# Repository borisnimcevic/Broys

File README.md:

# Watchular (ESP32-C3 based modular watch)

### Name origin:
* watch + modular

### Bill Of Materials
|Component  |Quantity |Link   |
|-----      |-----    |-----  |
|ESP32-C3   |1        |[digikey](https://www.digikey.se/en/products/detail/espressif-systems/ESP32-C3-MINI-1-N4-A/15817506) |
|or with embedded flash (ESP32-C3FN4)   |1        |[digikey](https://www.digikey.se/en/products/detail/espressif-systems/ESP32-C3FH4/14115592) |
|Battery charger|1        |[digikey](https://www.digikey.se/en/products/detail/microchip-technology/MCP73832T-2DCI-OT/1223150) |
|Battery connector|1        |[digikey](https://www.digikey.se/en/products/detail/w%C3%BCrth-elektronik/665102131822/5047757?s=N4IgTCBcDaIGxwKwEYAMZkGZkA4wQF0BfIA) |
|Button|2        |[digikey](https://www.digikey.se/en/products/detail/e-switch/TL3301AF260QG/378995?s=N4IgTCBcDaICoBkDMSAMBGAggMTANlQEUBxEAXQF8g) |
|Ceramic antenna (chip antenna)|1        |[digikey](https://www.digikey.se/en/products/detail/johanson-technology-inc/2450AT18A100E/1560676) |
|Ceramic capacitor 100nF 0402 |4        |[digikey](https://www.digikey.se/en/products/detail/taiyo-yuden/EMK105B7104KV-F/1004039) |
|Ceramic capacitor 1pF 0402 |1        |[digikey](https://www.digikey.se/en/products/detail/walsin-technology-corporation/0402N1R0B500CT/9354767) |
|Ceramic capacitor 1uF 0603 |2        |[digikey](https://www.digikey.se/en/products/detail/taiyo-yuden/EMK107BJ105KA-T/930603) |
|Ceramic capacitor 2.2uF 0603 |2        |[digikey](https://www.digikey.se/en/products/detail/taiyo-yuden/EMK107BJ225KA-T/1004018) |
|Ceramic capacitor 4.7uF 0402 |1        |[digikey](https://www.digikey.se/en/products/detail/murata-electronics/GRT155R60J475ME13J/13904800) |
|Ceramic capacitor 4.7uF 0603 |2        |[digikey](https://www.digikey.se/en/products/detail/taiyo-yuden/JMK107BJ475KA-T/1169922) |
|Ceramic capacitor 8pF 0402 |2        |[digikey](https://www.digikey.se/en/products/detail/taiyo-yuden/UMK105CH080DVHF/6563655) |
|Ceramic inductor 2.7nH |1        |[digikey](https://www.digikey.se/en/products/detail/johanson-technology-inc/L-07C2N7SV6T/1830166?s=N4IgTCBcDaIDIFoAMB2AwmAcigygNQDYAVEAXQF8g) |
|Ceramic inductor 3.9nH |1        |[digikey](https://www.digikey.se/en/products/detail/johanson-technology-inc/L-07C3N9SV6T/1915227) |
|Crystal 16MHz|1        |[digikey](https://www.digikey.se/en/products/detail/txc-corporation/8Y-16-000MAHQ-T/6130681) |
|FLASH 4MBIT   |1        |[digikey](https://www.digikey.se/en/products/detail/winbond-electronics/W25Q16JVSSIM/12143335) |
|LDO 3.3V 600mA|1        |[digikey](https://www.digikey.se/en/products/detail/diodes-incorporated/AP7366-33W5-7/9867322) |
|LED Orange 0402|1        |[digikey](https://www.digikey.se/en/products/detail/sunled/XZMOK68W-2/4902071) |
|LED Red 0603|30        |[digikey](https://www.digikey.se/en/products/detail/liteon/LTST-C191KRKT/386837) |
|Male Header 16 positions (1 row)|2        |[digikey](https://www.digikey.se/en/products/detail/adam-tech/PH1-16-UA/9830344) |
|N-channel MOSFET|4        |[digikey](https://www.digikey.se/en/products/detail/toshiba-semiconductor-and-storage/T2N7002AK-LM/5298028) |
|P-channel MOSFET|1        |[digikey](https://www.digikey.se/en/products/detail/diodes-incorporated/DMP2004K-7/1774201) |
|Resistor 0 ohm 0402   |1        |[digikey](https://www.digikey.se/en/products/detail/yageo/RC0402JR-070RP/4935294) |
|Resistor 100k 0402   |1        |[digikey](https://www.digikey.se/en/products/detail/yageo/RC0402JR-07100KL/726416) |
|Resistor 10k 0402   |4        |[digikey](https://www.digikey.se/en/products/detail/yageo/RC0402JR-0710KL/726418) |
|Resistor 1k 0402   |5        |[digikey](https://www.digikey.se/en/products/detail/delta-electronics-cyntec/PFR05S-102-JNH/9761533) |
|Resistor 2k 0402   |1        |[digikey](https://www.digikey.se/en/products/detail/yageo/RC0402JR-072KL/726434) |
|Resistor 5.1k 1% 0402   |2        |[digikey](https://www.digikey.se/en/products/detail/yageo/RC0402FR-135K1L/14286364) |
|Resistor 560 0402   |9        |[digikey](https://www.digikey.se/en/products/detail/yageo/RC0402JR-07560RL/726492) |
|Schottky|1        |[digikey](https://www.digikey.se/en/products/detail/smc-diode-solutions/DSS16U/8341861) |
|USB-C|1        |[digikey](https://www.digikey.se/en/products/detail/gct/USB4105-GF-A/11198441) |
|ESD-protector|1        |[digikey](https://www.digikey.se/en/products/detail/smc-diode-solutions/SR05/10820120) |

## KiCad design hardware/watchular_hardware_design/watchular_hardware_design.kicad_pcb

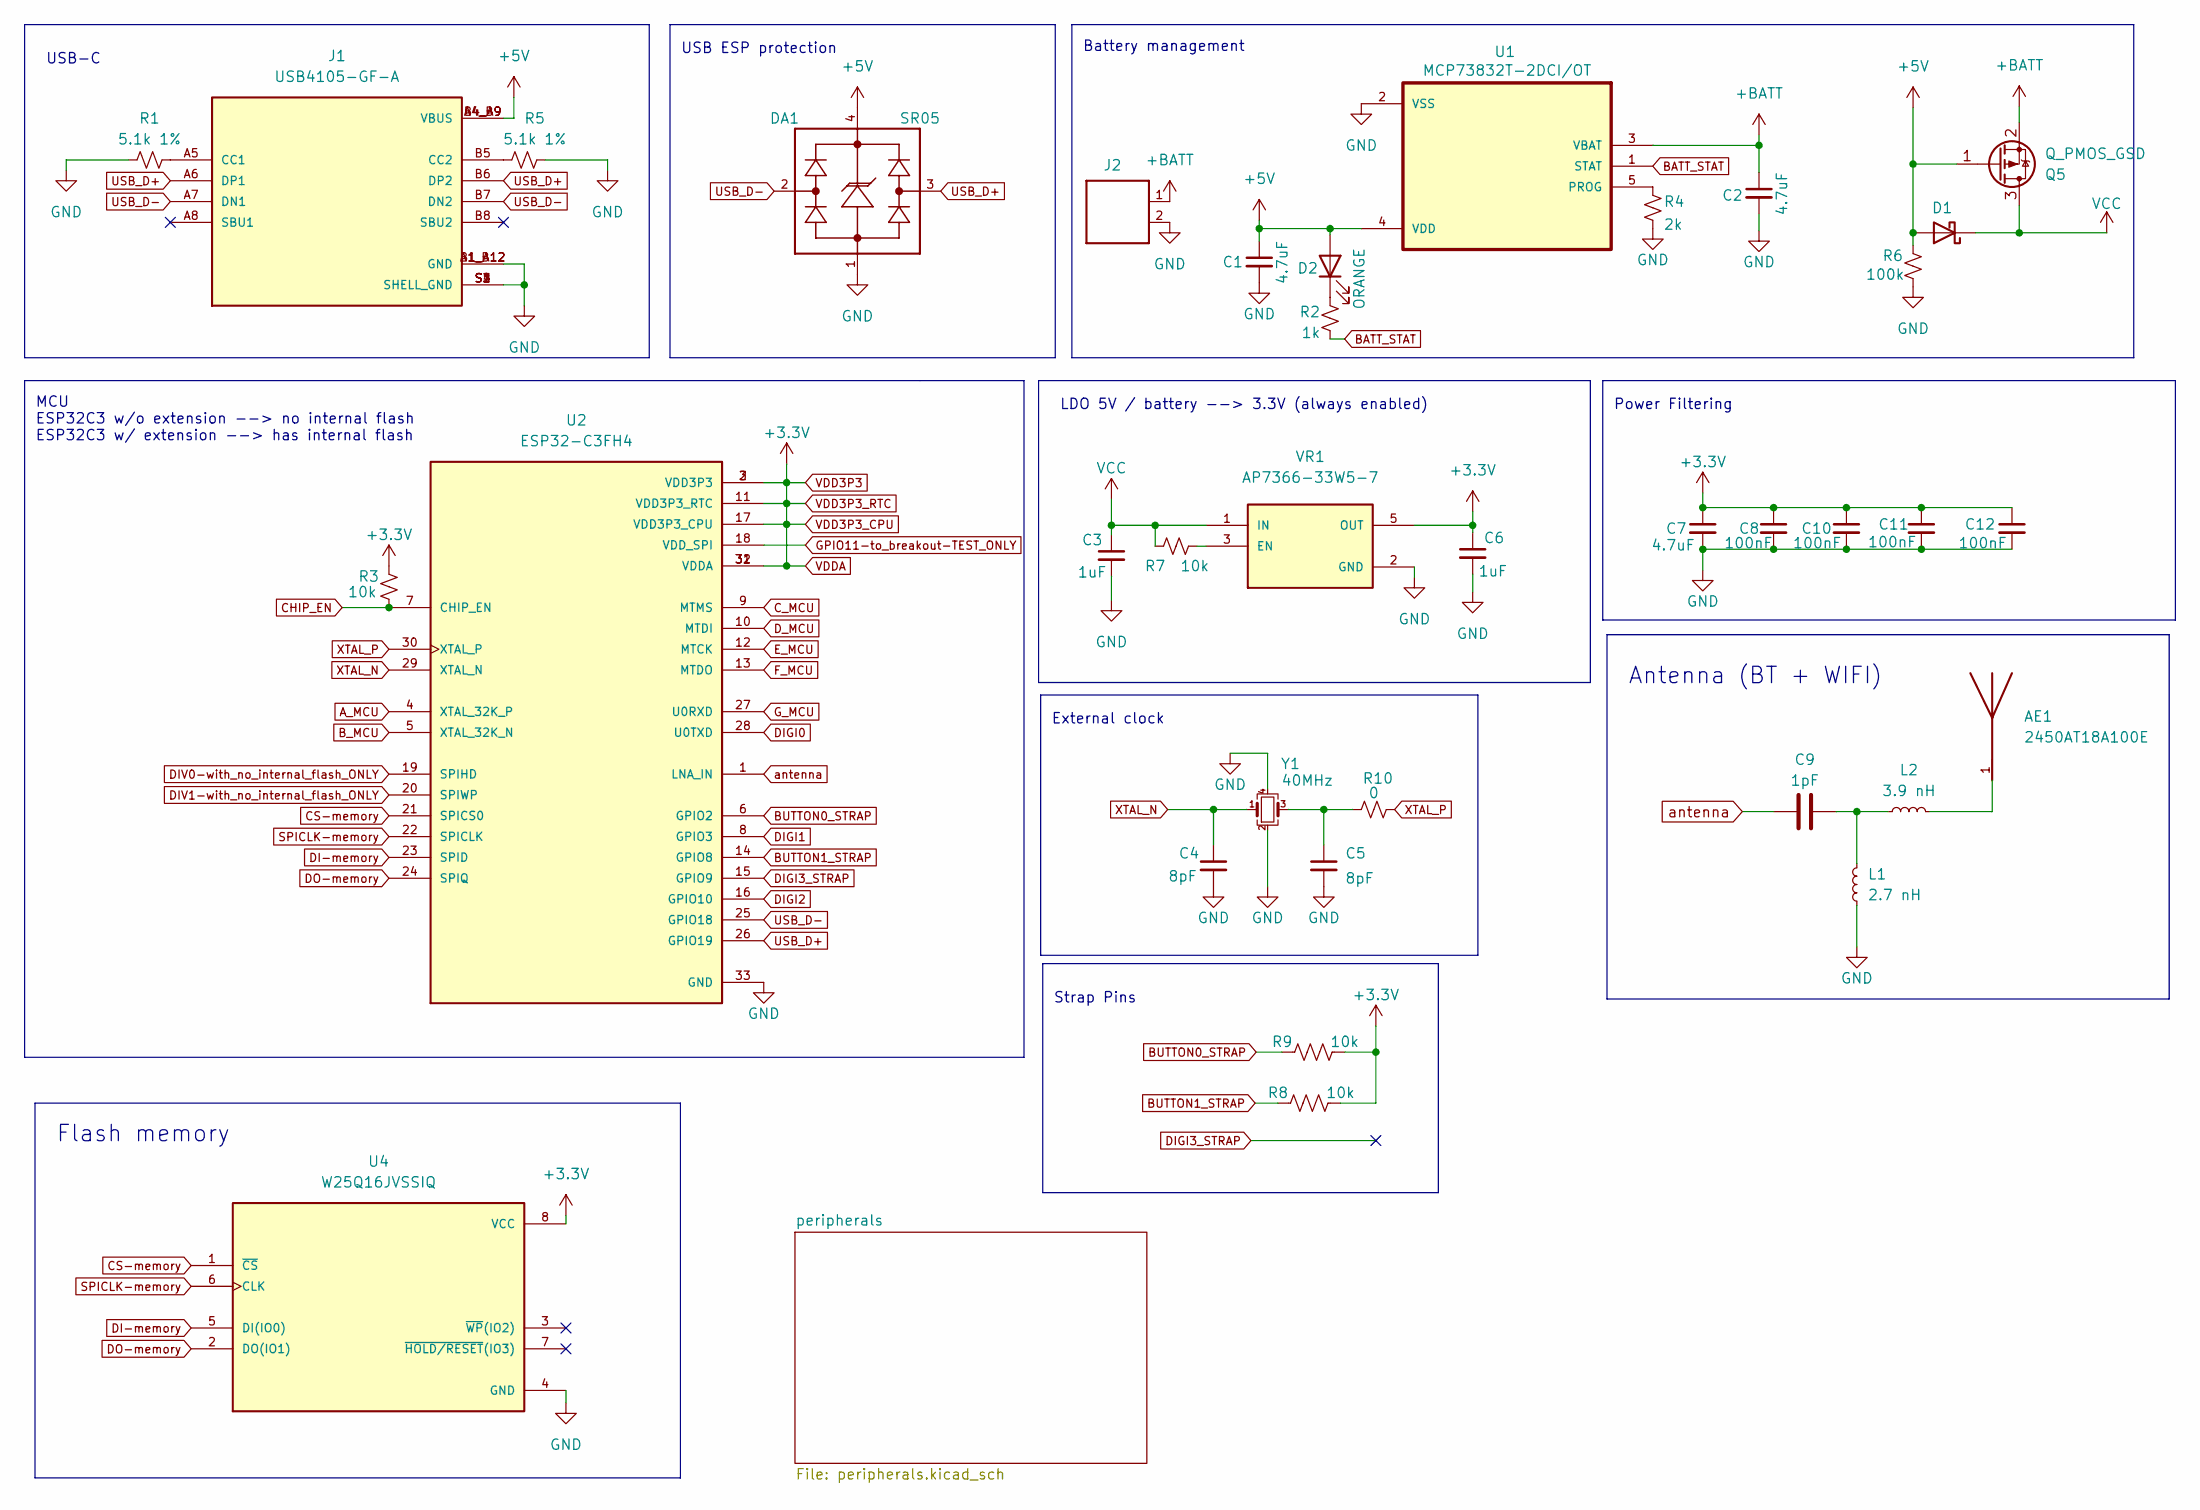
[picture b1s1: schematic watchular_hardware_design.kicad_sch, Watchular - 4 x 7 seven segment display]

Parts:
AE1: 2450AT18A100E; ANTC3216X140N; PARTREV 1.3
C1, C2: 4.7uF; C_0603_1608Metric_Pad1.08x0.95mm_HandSolder
C3, C6: 1uF; C_0603_1608Metric_Pad1.08x0.95mm_HandSolder
C4, C5: 8pF; C_0402_1005Metric_Pad0.74x0.62mm_HandSolder
C7: 4.7uF; L_0402_1005Metric
C8, C10, C11, C12: 100nF; L_0402_1005Metric
C9: 1pF; C_0402_1005Metric
D1: D_Schottky; D_SOD-123F
D2: ORANGE; LED_0402_1005Metric_Pad0.77x0.64mm_HandSolder
DA1: SR05; SOT143
J1: USB4105-GF-A; GCT_USB4105-GF-A; PARTREV A3
J2: 665102131822
L1: 2.7 nH; L_0402_1005Metric
L2: 3.9 nH; L_0402_1005Metric
Q5: Q_PMOS_GSD; SOT91P240X105-3N
R1, R5: 5.1k 1%; R_0402_1005Metric_Pad0.72x0.64mm_HandSolder
R2: 1k; R_0402_1005Metric_Pad0.72x0.64mm_HandSolder
R3, R7, R8, R9: 10k; R_0402_1005Metric_Pad0.72x0.64mm_HandSolder
R4: 2k; R_0402_1005Metric_Pad0.72x0.64mm_HandSolder
R6: 100k; R_0402_1005Metric_Pad0.72x0.64mm_HandSolder
R10: 0; R_0402_1005Metric_Pad0.72x0.64mm_HandSolder
U1: MCP73832T-2DCI/OT; SOT95P280X145-5N
U2: ESP32-C3FH4; QFN50P500X500X90-33N; PARTREV V1.0
U4: W25Q16JVSSIQ; SOIC127P790X216-8N
VR1: AP7366-33W5-7; SOT95P285X140-5N; PARTREV 1-2
Y1: 40MHz; Crystal_SMD_2016-4Pin_2.0x1.6mm

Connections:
+5V: C1.1, D1.2 (A), D2.2 (A), DA1.4, J1.A4_B9 (VBUS), J1.B4_A9 (VBUS), Q5.1 (G), R6.1, U1.4 (VDD); also elsewhere on the board
+BATT: C2.1, J2.1, Q5.2 (S), U1.3 (VBAT); also elsewhere on the board
A_MCU: U2.4 (XTAL_32K_P); also elsewhere on the board
BATT_STAT: R2.2, U1.1 (STAT)
BUTTON0_STRAP: R9.1, U2.6 (GPIO2); also elsewhere on the board
BUTTON1_STRAP: R8.1, U2.14 (GPIO8); also elsewhere on the board
B_MCU: U2.5 (XTAL_32K_N); also elsewhere on the board
CHIP_EN: R3.2, U2.7 (CHIP_EN); also elsewhere on the board
CS-memory: U2.21 (SPICS0), U4.1 (~CS); also elsewhere on the board
C_MCU: U2.9 (MTMS); also elsewhere on the board
DI-memory: U2.23 (SPID), U4.5 (DI(IO0)); also elsewhere on the board
DIGI0: U2.28 (U0TXD); also elsewhere on the board
DIGI1: U2.8 (GPIO3); also elsewhere on the board
DIGI2: U2.16 (GPIO10); also elsewhere on the board
DIGI3_STRAP: U2.15 (GPIO9); also elsewhere on the board
DIV0-with_no_internal_flash_ONLY: U2.19 (SPIHD); also elsewhere on the board
DIV1-with_no_internal_flash_ONLY: U2.20 (SPIWP); also elsewhere on the board
DO-memory: U2.24 (SPIQ), U4.2 (DO(IO1)); also elsewhere on the board
D_MCU: U2.10 (MTDI); also elsewhere on the board
E_MCU: U2.12 (MTCK); also elsewhere on the board
F_MCU: U2.13 (MTDO); also elsewhere on the board
GND: C1.2, C2.2, C3.2, C4.2, C5.2, C6.2, C7.2, C8.2, C10.2, C11.2, C12.2, DA1.1, J1.A1_B12 (GND), J1.B1_A12 (GND), J1.S1 (SHELL_GND), J1.S2 (SHELL_GND), J1.S3 (SHELL_GND), J1.S4 (SHELL_GND), J2.2, L1.1, R1.1, R4.2, R5.2, R6.2, U1.2 (VSS), U2.33 (GND), U4.4 (GND), VR1.2 (GND), Y1.2, Y1.4; also elsewhere on the board
GPIO11-to_breakout-TEST_ONLY: U2.18 (VDD_SPI); also elsewhere on the board
G_MCU: U2.27 (U0RXD); also elsewhere on the board
unnamed: AE1.1, L2.2
unnamed: C5.1, R10.1, Y1.3
unnamed: C9.2, L1.2, L2.1
unnamed: D2.1 (K), R2.1
unnamed: J1.A5 (CC1), R1.2
unnamed: J1.B5 (CC2), R5.1
unnamed: R4.1, U1.5 (PROG)
unnamed: R7.2, VR1.3 (EN)
SPICLK-memory: U2.22 (SPICLK), U4.6 (CLK); also elsewhere on the board
USB_D+: DA1.3, J1.A6 (DP1), J1.B6 (DP2), U2.26 (GPIO19); also elsewhere on the board
USB_D-: DA1.2, J1.A7 (DN1), J1.B7 (DN2), U2.25 (GPIO18); also elsewhere on the board
VCC: C3.1, D1.1 (K), Q5.3 (D), R7.1, VR1.1 (IN)
VDD3P3: C6.1, C7.1, C8.1, C10.1, C11.1, C12.1, R3.1, R8.2, R9.2, U2.2 (VDD3P3), U2.3 (VDD3P3), U2.11 (VDD3P3_RTC), U2.17 (VDD3P3_CPU), U2.31 (VDDA), U2.32 (VDDA), U4.8 (VCC), VR1.5 (OUT); also elsewhere on the board
XTAL_N: C4.1, U2.29 (XTAL_N), Y1.1; also elsewhere on the board
XTAL_P: R10.2, U2.30 (XTAL_P); also elsewhere on the board
antenna: C9.1, U2.1 (LNA_IN)

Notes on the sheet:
USB-C
LDO 5V / battery --> 3.3V (always enabled)
Battery management
Flash memory
Power Filtering
Antenna (BT + WIFI)
External clock
MCU ESP32C3 w/o extension --> no internal flash ESP32C3 w/ extension --> has internal flash
Strap Pins
USB ESP protection

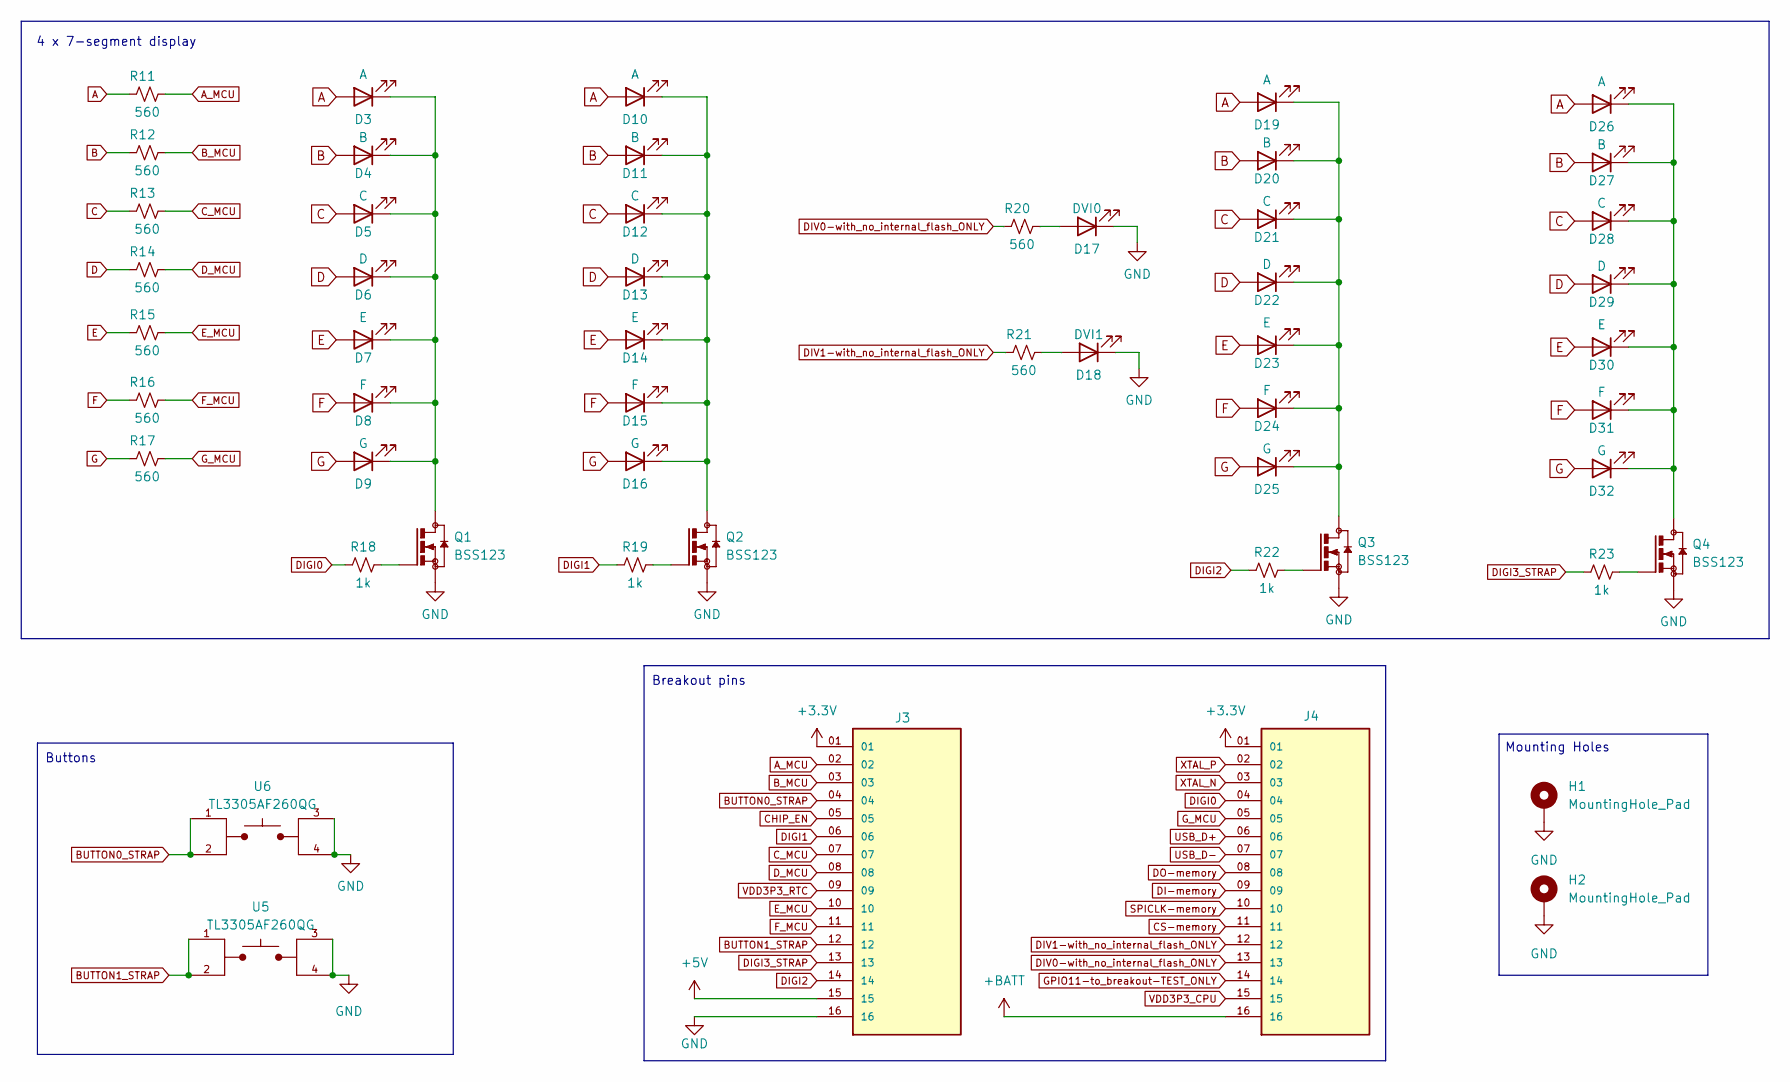
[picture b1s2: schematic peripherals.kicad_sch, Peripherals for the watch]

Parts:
D3, D10, D19, D26: A; LED_0603_custom_boris
D4, D11, D20, D27: B; LED_0603_custom_boris
D5, D12, D21, D28: C; LED_0603_custom_boris
D6, D13, D22, D29: D; LED_0603_custom_boris
D7, D14, D23, D30: E; LED_0603_custom_boris
D8, D15, D24, D31: F; LED_0603_custom_boris
D9, D16, D25, D32: G; LED_0603_custom_boris
D17: DVI0; LED_0603_custom_boris
D18: DVI1; LED_0603_custom_boris
H1, H2: MountingHole_Pad; MountingHole_2.2mm_M2_Pad_Via
J3, J4: TSW-116-07-H-S; SAMTEC_TSW-116-07-H-S; PARTREV R
Q1, Q2, Q3, Q4: BSS123; SOT23
R11, R12, R13, R14, R15, R16, R17, R20, R21: 560; R_0402_1005Metric_Pad0.72x0.64mm_HandSolder
R18, R19, R22, R23: 1k; R_0402_1005Metric_Pad0.72x0.64mm_HandSolder
U5, U6: TL3305AF260QG; SW_TL3305AF260QG; PARTREV C

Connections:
+5V: J3.15; also elsewhere on the board
+BATT: J4.16; also elsewhere on the board
A: D3.2 (A), D10.2 (A), D19.2 (A), D26.2 (A), R11.1
A_MCU: J3.02, R11.2; also elsewhere on the board
B: D4.2 (A), D11.2 (A), D20.2 (A), D27.2 (A), R12.1
BUTTON0_STRAP: J3.04, U6.1, U6.2; also elsewhere on the board
BUTTON1_STRAP: J3.12, U5.1, U5.2; also elsewhere on the board
B_MCU: J3.03, R12.2; also elsewhere on the board
C: D5.2 (A), D12.2 (A), D21.2 (A), D28.2 (A), R13.1
CHIP_EN: J3.05; also elsewhere on the board
CS-memory: J4.11; also elsewhere on the board
C_MCU: J3.07, R13.2; also elsewhere on the board
D: D6.2 (A), D13.2 (A), D22.2 (A), D29.2 (A), R14.1
DI-memory: J4.09; also elsewhere on the board
DIGI0: J4.04, R18.1; also elsewhere on the board
DIGI1: J3.06, R19.1; also elsewhere on the board
DIGI2: J3.14, R22.1; also elsewhere on the board
DIGI3_STRAP: J3.13, R23.1; also elsewhere on the board
DIV0-with_no_internal_flash_ONLY: J4.13, R20.1; also elsewhere on the board
DIV1-with_no_internal_flash_ONLY: J4.12, R21.1; also elsewhere on the board
DO-memory: J4.08; also elsewhere on the board
D_MCU: J3.08, R14.2; also elsewhere on the board
E: D7.2 (A), D14.2 (A), D23.2 (A), D30.2 (A), R15.1
E_MCU: J3.10, R15.2; also elsewhere on the board
F: D8.2 (A), D15.2 (A), D24.2 (A), D31.2 (A), R16.1
F_MCU: J3.11, R16.2; also elsewhere on the board
G: D9.2 (A), D16.2 (A), D25.2 (A), D32.2 (A), R17.1
GND: D17.1 (K), D18.1 (K), H1.1, H2.1, J3.16, Q1.2, Q2.2, Q3.2, Q4.2, U5.3, U5.4, U6.3, U6.4; also elsewhere on the board
GPIO11-to_breakout-TEST_ONLY: J4.14; also elsewhere on the board
G_MCU: J4.05, R17.2; also elsewhere on the board
unnamed: D3.1 (K), D4.1 (K), D5.1 (K), D6.1 (K), D7.1 (K), D8.1 (K), D9.1 (K), Q1.3
unnamed: D10.1 (K), D11.1 (K), D12.1 (K), D13.1 (K), D14.1 (K), D15.1 (K), D16.1 (K), Q2.3
unnamed: D17.2 (A), R20.2
unnamed: D18.2 (A), R21.2
unnamed: D19.1 (K), D20.1 (K), D21.1 (K), D22.1 (K), D23.1 (K), D24.1 (K), D25.1 (K), Q3.3
unnamed: D26.1 (K), D27.1 (K), D28.1 (K), D29.1 (K), D30.1 (K), D31.1 (K), D32.1 (K), Q4.3
unnamed: Q1.1, R18.2
unnamed: Q2.1, R19.2
unnamed: Q3.1, R22.2
unnamed: Q4.1, R23.2
SPICLK-memory: J4.10; also elsewhere on the board
USB_D+: J4.06; also elsewhere on the board
USB_D-: J4.07; also elsewhere on the board
VDD3P3: J3.01, J3.09, J4.01, J4.15; also elsewhere on the board
XTAL_N: J4.03; also elsewhere on the board
XTAL_P: J4.02; also elsewhere on the board

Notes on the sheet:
Breakout pins
4 x 7-segment display
Buttons
Mounting Holes

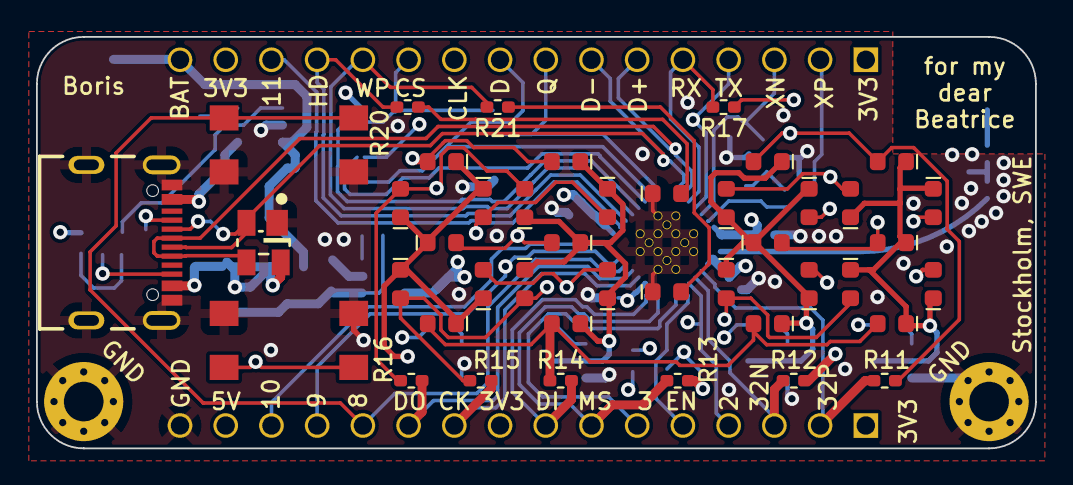
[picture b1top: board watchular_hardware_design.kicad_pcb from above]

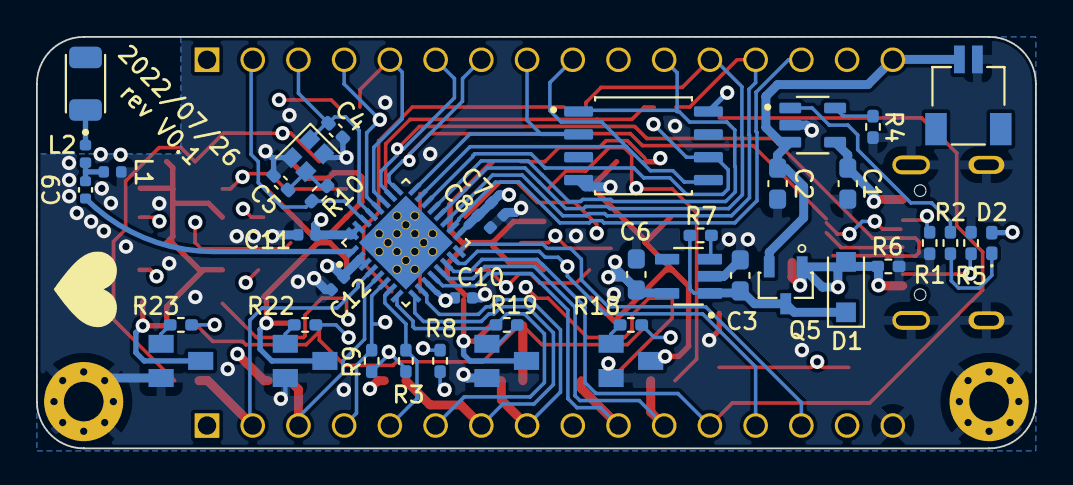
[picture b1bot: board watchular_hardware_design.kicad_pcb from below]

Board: 4 copper layers, 55.5 x 22.9 mm, 89 parts (42 on the bottom side), 57 nets.

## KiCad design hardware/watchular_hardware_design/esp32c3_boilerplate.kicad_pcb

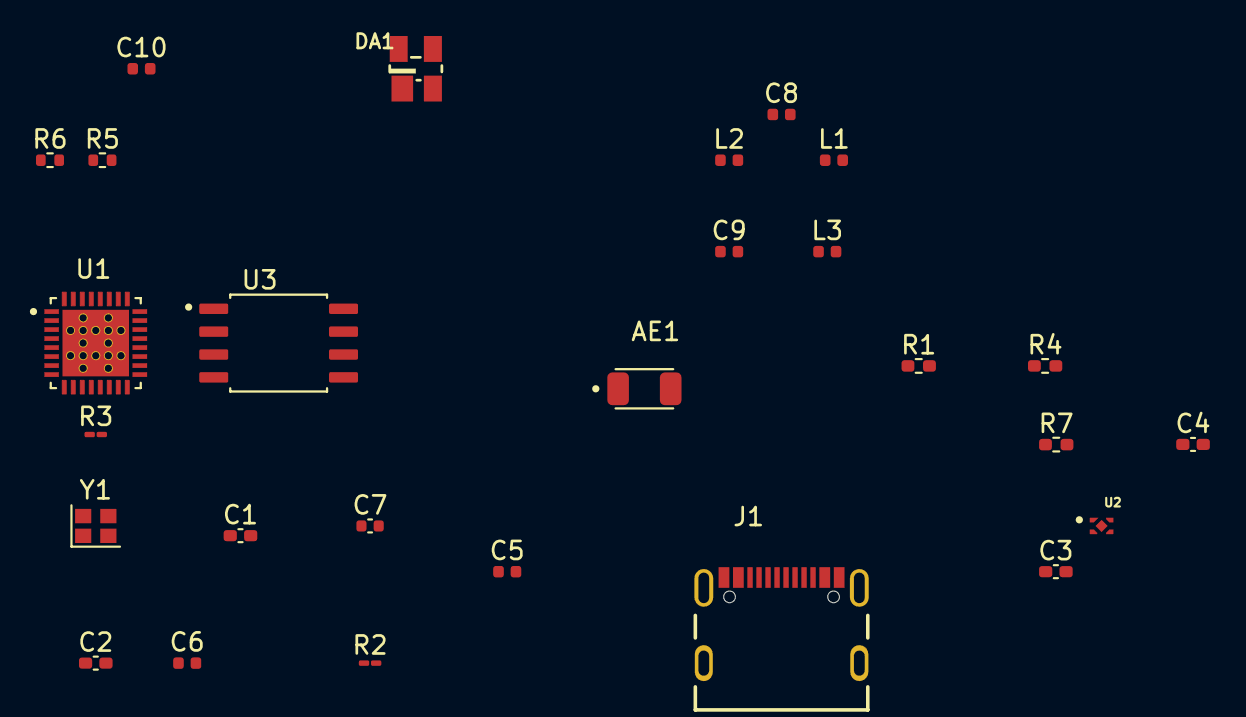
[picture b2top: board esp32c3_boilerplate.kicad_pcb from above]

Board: 2 copper layers, 27 parts (0 on the bottom side), 22 nets, no tracks yet.

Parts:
AE1: 2450AT18A100E; ANTC3216X140N
C1, C2: 8pF; C_0402_1005Metric_Pad0.74x0.62mm_HandSolder
C3, C4: 2.2uF; C_0402_1005Metric_Pad0.74x0.62mm_HandSolder
C5: 4.7uF; L_0402_1005Metric
C6, C8: 100nF; L_0402_1005Metric
C7: 1pF; C_0402_1005Metric
C9: 1uF; L_0402_1005Metric
C10: 10nF; L_0402_1005Metric
DA1: SR05; SOT143
J1: USB4105-GF-A; GCT_USB4105-GF-A
L1: 2.7 nH; L_0402_1005Metric
L2: 3.9 nH; L_0402_1005Metric
L3: 39nH; L_0402_1005Metric
R1, R4: 5.1k 1%; R_0402_1005Metric_Pad0.72x0.64mm_HandSolder
R2: 0; R_01005_0402Metric_Pad0.57x0.30mm_HandSolder
R3: 10k; R_01005_0402Metric_Pad0.57x0.30mm_HandSolder
R5, R6: 10k; R_0402_1005Metric
R7: 10k; R_0402_1005Metric_Pad0.72x0.64mm_HandSolder
U1: ESP32-C3FH4; QFN50P500X500X90-33N
U2: MIC5524-3.3YMT-TZ; VREG_MIC5524-3.3YMT-TZ
U3: W25Q16JVSSIQ; SOIC127P790X216-8N
Y1: 40MHz; Crystal_SMD_2016-4Pin_2.0x1.6mm

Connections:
+3.3VA: C9.1, C10.1, L3.2, U1.2 (VDD3P3), U1.3 (VDD3P3), U1.31 (VDDA), U1.32 (VDDA)
+3V3: C4.1, C5.1, C6.1, C8.1, L3.1, R3.1, R5.2, R6.2, U1.11 (VDD3P3_RTC), U1.17 (VDD3P3_CPU), U2.1 (VOUT), U3.8 (VCC)
+5V: C3.1, DA1.4, J1.A4_B9 (VBUS), J1.B4_A9 (VBUS), R7.1, U2.4 (VIN)
CS-memory: U1.21 (SPICS0), U3.1 (~CS)
DI-memory: U1.23 (SPID), U3.5 (DI(IO0))
DO-memory: U1.24 (SPIQ), U3.2 (DO(IO1))
GND: C1.2, C2.2, C3.2, C4.2, C5.2, C6.2, C8.2, C9.2, C10.2, DA1.1, J1.A1_B12 (GND), J1.B1_A12 (GND), J1.S1 (SHELL_GND), J1.S2 (SHELL_GND), J1.S3 (SHELL_GND), J1.S4 (SHELL_GND), L1.1, R1.1, R4.2, U1.33 (GND), U2.2 (GND), U2.EP (EXP), U3.4 (GND), Y1.2, Y1.4
GPIO2_STRAP: R6.1, U1.6 (GPIO2)
GPIO8_STRAP: R5.1, U1.14 (GPIO8)
unnamed: AE1.1, L2.2
unnamed: C2.1, R2.1, Y1.3
unnamed: C7.2, L1.2, L2.1
unnamed: J1.A5 (CC1), R1.2
unnamed: J1.B5 (CC2), R4.1
unnamed: R3.2, U1.7 (CHIP_EN)
unnamed: R7.2, U2.3 (EN)
SPICLK-memory: U1.22 (SPICLK), U3.6 (CLK)
USB_D+: DA1.3, J1.A6 (DP1), J1.B6 (DP2), U1.26 (GPIO19)
USB_D-: DA1.2, J1.A7 (DN1), J1.B7 (DN2), U1.25 (GPIO18)
XTAL_N: R2.2, U1.29 (XTAL_N)
XTAL_P: C1.1, U1.30 (XTAL_P), Y1.1
antenna: C7.1, U1.1 (LNA_IN)

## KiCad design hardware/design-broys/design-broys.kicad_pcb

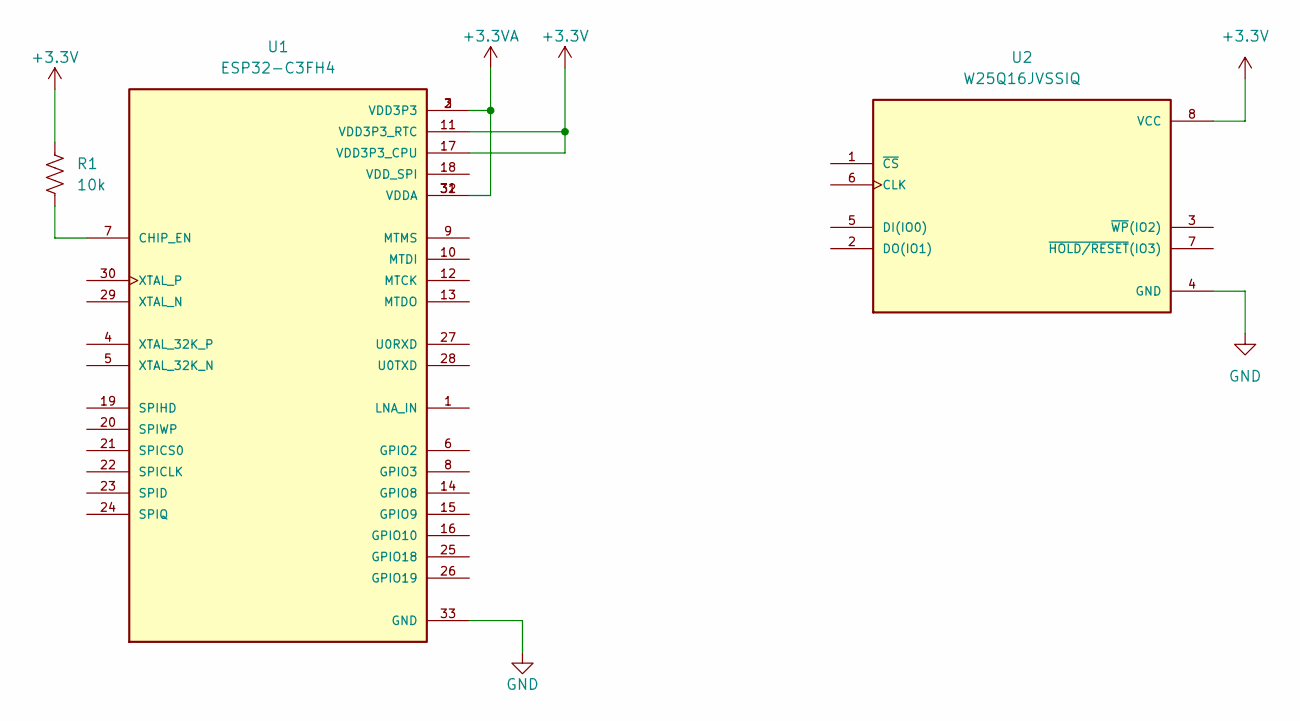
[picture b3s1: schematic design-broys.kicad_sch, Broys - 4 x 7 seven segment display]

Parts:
R1: 10k; R_0402_1005Metric
U1: ESP32-C3FH4; QFN50P500X500X90-33N; PARTREV V1.0
U2: W25Q16JVSSIQ; SOIC127P790X216-8N

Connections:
+3.3VA: U1.2 (VDD3P3), U1.3 (VDD3P3), U1.31 (VDDA), U1.32 (VDDA)
+3V3: R1.1, U1.11 (VDD3P3_RTC), U1.17 (VDD3P3_CPU), U2.8 (VCC)
GND: U1.33 (GND), U2.4 (GND)
unnamed: R1.2, U1.7 (CHIP_EN)

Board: 2 copper layers, 3 parts (0 on the bottom side), 4 nets, no tracks yet.

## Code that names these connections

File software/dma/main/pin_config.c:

#include "pin_config.h"
#include "stdint.h"

void initGPIOs(void) {
  uint64_t bit_mask =
      0; /*!< GPIO pin: set with bit mask, each bit maps to a GPIO */
  for (uint8_t i = 0; i < sizeof(digit_pins) / sizeof(gpio_num_t); i++) {
    bit_mask |= (1ULL << digit_pins[i]);
  }
  for (uint8_t i = 0; i < sizeof(led_pins) / sizeof(gpio_num_t); i++) {
    bit_mask |= (1ULL << led_pins[i]);
  }
  gpio_config_t io_conf;
  io_conf.intr_type = GPIO_INTR_DISABLE;
  io_conf.mode = GPIO_MODE_OUTPUT;
  io_conf.pin_bit_mask = bit_mask;
  io_conf.pull_down_en = 0;
  io_conf.pull_up_en = 0;
  gpio_config(&io_conf);
}

// void setPlace(const uint8_t place) {
//   const uint8_t mask = (place <= 3) ? (1 << place) : 0;
//   const uint8_t val = mask & 0x0F;
//   gpio_set_level(DIGI0, val & 0x1);
//   gpio_set_level(DIGI1, val & 0x2);
//   gpio_set_level(DIGI2, val & 0x4);
//   gpio_set_level(DIGI3, val & 0x8);
// }
//
// void setDigit(const uint8_t digit) {
//   const uint8_t *val = (digit <= 9) ? values[digit] : values[10];
//   for (int i = 0; i < 7; i++) {
//     gpio_set_level(led_pins[i], val[i]);
//   }
// }

void clearLED(void) {
  setPlace(PIN_MAX_DIGIT + 1);
  setDigit(PIN_MAX_NUMBER + 1);
}

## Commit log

2022-06-02 Init repo
2022-06-02 Add readme
2022-06-02 Added esp32
2022-06-02 Updated gitignore with kicad gitignore.
2022-06-02 Added external 16MBit flash
2022-06-11 Added technical reference manual for the esp.
2022-06-11 Added power supplies on the esp32
2022-06-11 Added datasheet for the resistors.
2022-06-11 Added memory
2022-06-11 Added memory to the schematic.
2022-06-11 Fixed the issue with kicad versioning
2022-06-12 Connected flash with the esp.
2022-06-13 Added resistor and leds to the BOM.
2022-06-13 Added LEDs for the first digit.
2022-06-13 renaming the project
2022-06-13 Added datasheet for the red LED.
2022-06-13 Added LED driving resistor.
2022-06-13 Added resistors for the LEDs but alrady running into the IO count problem.
2022-06-14 Configured boot strapping pins
2022-06-14 Added ceramic chip antenna to the project.
2022-06-14 Added antenna to the BOM
2022-06-15 Added antenna to the MCU
2022-06-15 Made analog filter for VDD3P3.
2022-06-15 Added connections for XTAL_32K_P and XTAL_32K_N
2022-06-15 Connected GPIO2
2022-06-15 Added caps for 3.3V for VDD3P3_RTC
2022-06-15 XTAL left to be connected
2022-06-16 Finished the boiler plate for ESP32C3.
2022-06-16 Clean up the schematic.
2022-06-16 Imported the USB-C
2022-06-16 Wired up the USB-C
2022-06-17 Added and wired up the LDO. Boiler plate done.
2022-06-17 Removed LEDs
2022-06-17 Updated the file naming to the boiler plate.
2022-06-17 Fixing the typo.
2022-06-18 Added ESD protection on the USB.
2022-06-19 Coppied to another git repo. Ready to merge.
2022-06-19 Test merge
2022-06-20 Added ESD protection to the USB.
2022-06-20 Added current limiting resistors and connected to MCU.
2022-06-21 Added components for 4 digits.
2022-06-22 Added MOSFET-BSS123 to the project.
2022-06-22 Added MOSFET to all 4 digits.
2022-06-22 Imported button library.
2022-06-22 Updated readme with the button link.
2022-06-29 Connected buttons.
2022-06-29 Added a 16 position header.
2022-07-03 Added 15 position 2.45mm headers.
2022-07-03 Connected MCU pins to the brekout 15 pos header.
2022-07-06 Added battery connector.
2022-07-06 Added battery charger.
2022-07-06 Added link to the battery charger.
2022-07-06 Added mosfet for controlling the power source.
2022-07-06 Added schottky diode.
2022-07-06 Added datasheet for the schottky.
2022-07-06 Dual power wired up
2022-07-06 Added back the 16 pin headers.
2022-07-06 Schematic is done for now.
2022-07-07 Started exploring the PCB editor.
2022-07-08 Set the board size to adafruit feather size.
2022-07-10 Started work on the PCB
2022-07-11 Need to make put components on both sides...
2022-07-12 Added mouting holes and assigned footprints.
2022-07-13 Bottom side elements first arrangement.
2022-07-13 USB and antenna locked.
2022-07-14 Locked the board size.
2022-07-14 Poured the inner planes.
2022-07-14 Imported a bit smaller buttons.
2022-07-14 Locked the first digit.
2022-07-14 Made a small calculator for the LED positions.
2022-07-14 Digits and holes locked
2022-07-14 One arc around the screw done.
2022-07-15 Added rounded edges around the screws.
2022-07-15 Made all 4 corners rounded.
2022-07-15 Battery management section in place.
2022-07-15 Moded digits to the middle.
2022-07-15 Places LED drivers.
2022-07-15 All the components are on the board.
2022-07-15 Front panel fixed.
2022-07-16 Let the routing begin.
2022-07-17 Added 3d for headers. Fixed all the errors.
2022-07-17 Routed memory and USB.
2022-07-17 Bottom side routing in progress...
2022-07-18 All CPU pins connected to the breakout.
2022-07-18 2 digits wired in.
2022-07-20 Figuring out the top side...
2022-07-20 Looking for alternatives.
2022-07-21 Removed the filtering circuit for the VDDA to save space.
2022-07-21 All the numbers are wired up.
2022-07-21 Drivers for right two digits wired in.
2022-07-21 Added pour zones to all the layers.
2022-07-21 All the digits connected.
2022-07-21 Buttons wired in.
2022-07-21 Aligned the resistors on the front side.
2022-07-21 Started wiring the power part.
2022-07-22 Added 5V pouring area.
2022-07-22 Everything connected.
2022-07-22 No errors on the DRC.
2022-07-22 Added back the 0402 resistors.
2022-07-22 Removed silkscreen for the hearders.
2022-07-22 Fixed the USBC position.
2022-07-23 Added labels for the breakot.
2022-07-23 Added bypass cap to pin 11.
2022-07-23 Shortening a lot of wires.
2022-07-24 Refactoring.
2022-07-25 Resized back the board to the original size.
2022-07-25 Updated the footprint for LEDs
2022-07-25 Cleand up top traces.
2022-07-25 Cleand up the bottom copper layer.
2022-07-26 Added stitching vias.
2022-07-26 Cleaned up the tracks.
2022-07-26 Top side silkscreen done.
2022-07-26 Fixed the silk screen on the bottom.
2022-07-26 Connected A to B USB pads. No errors or warnings.
2022-07-26 Added date, company name, place and version.
2022-07-26 Added open hardwre logo. Ready for the order.
2022-07-27 Started the BOM.
2022-07-27 Updated the MOSFTES.
2022-07-27 LDO not in stock. Need new one.
2022-07-28 Found suitable LDO (AP7366-33W5-7).
2022-07-28 Updated desing with a suitable LDO.
2022-08-01 Submin for PCB design.
2022-08-01 Added custom graphics.
2022-10-16 sorted BOM
2022-10-16 updated BOM
2023-02-03 Project to test the hardware
2023-02-03 Updated gitignore with the esp stuff
2023-02-03 controlling all the digit LEDs
2023-02-03 added datasheet for the crystal
2023-02-03 ignore vscode
2023-02-21 added pin_config
2023-03-02 Manipulating GPIO_REG
2023-03-02 async memcpy can't work
2023-03-02 Switched to the new KiCAD version.
2023-03-02 WIP using tasks, but the dog is not happy
2023-03-06 DMA is not possible
2023-03-06 added functions for setting the digit and the place
2023-03-06 Cleaned up the functions
2023-03-06 ISR working and digits are not flickering
2023-03-06 Counter couting up
2023-03-07 polishing
2023-03-07 Connected to wifi
